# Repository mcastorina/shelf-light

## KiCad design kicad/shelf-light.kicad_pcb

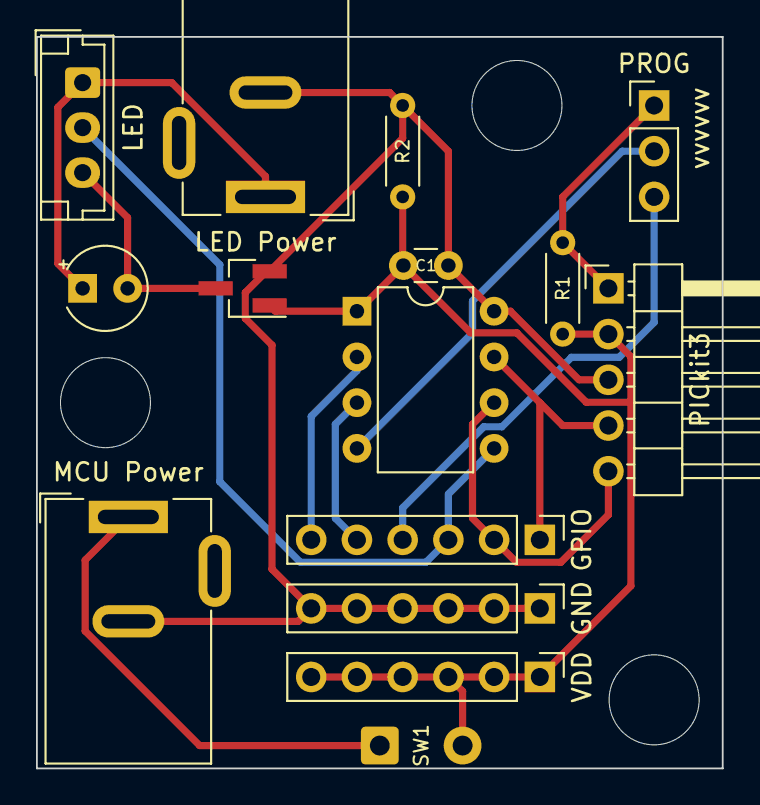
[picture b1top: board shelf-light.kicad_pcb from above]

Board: 2 copper layers, 38.1 x 40.6 mm, 18 parts (0 on the bottom side), 13 nets.

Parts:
C1: 100nF; C_Disc_D3.0mm_W1.6mm_P2.50mm
C2: 100mF; CP_Radial_Tantal_D4.5mm_P2.50mm
GND: GND; PinHeader_1x06_P2.54mm_Vertical
GPIO: GPIO; PinHeader_1x06_P2.54mm_Vertical
H1, H2, H3: MountingHole; MountingHole_5mm
LED: LED; JST_EH_B3B-EH-A_1x03_P2.50mm_Vertical
LED Power: LED Power; BarrelJack_Wuerth_6941xx301002
MCU Power: MCU Power; BarrelJack_Wuerth_6941xx301002
PICkit3: PICkit3; PinHeader_1x05_P2.54mm_Horizontal
PROG: vvvvvv; PinHeader_1x03_P2.54mm_Vertical
Q1: NDS355AN; SOT-23_Handsoldering
R1, R2: 10k; R_Axial_DIN0204_L3.6mm_D1.6mm_P5.08mm_Horizontal
SW1: Switch; SolderWire-0.5sqmm_1x02_P4.6mm_D0.9mm_OD2.1mm
U1: PIC16F15313; DIP-8_W7.62mm
VDD: VDD; PinHeader_1x06_P2.54mm_Vertical

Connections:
GND: C1.1, GND.1, GND.2, GND.3, GND.4, GND.5, GND.6, LED Power.2, MCU Power.2, PICkit3.3, Q1.2, R2.2, U1.8
unnamed: C2.1, LED.1, LED Power.1
unnamed: C2.2, LED.3, Q1.3
unnamed: PICkit3.1, PROG.1, R1.2
unnamed: GPIO.1, PICkit3.4, U1.7
unnamed: GPIO.2, PICkit3.5, U1.6
unnamed: MCU Power.1, SW1.1
unnamed: GPIO.3, LED.2, U1.5
unnamed: GPIO.4, PROG.3
unnamed: GPIO.5, U1.3
unnamed: GPIO.6, U1.2
unnamed: PROG.2, U1.4
VDD: C1.2, PICkit3.2, Q1.1, R1.1, R2.1, SW1.2, U1.1, VDD.1, VDD.2, VDD.3, VDD.4, VDD.5, VDD.6

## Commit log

2020-09-07 Arduino POC
    This sketch uses a potentiometer to calculate the warmth value as a
    function of hue. Hue is then converted to RGB, and a library writes the
    data to the LED strip.
2020-09-09 Implement stable analog read
    To get a stable reading, we take the average of 10 successive reads.
2020-09-09 Update the LED strip only if the color has changed
2020-09-09 Use low power sleep instead of delay
2020-09-10 Add current measurements
2020-10-10 Add MPLabX project for programming the PIC
    The main.c file successfully writes to the LED strip, but needs to be
    expanded to include reading the potentiometer and dynamically updating
    the color.
2020-10-10 Add gitignore for arduino-uno
2020-10-12 Implement analog read and color changing logic
    The ADC is configured to read an analog value from RA4 using Vdd as a
    voltage reference. That value is then converted to a number between 120
    and 360 to be used as the hue value in HSV to RGB conversion.
    Converting from HSV normally uses floating points, but to save
    programming memory it is implemented as fixed point with two decimal
    places.
2020-10-15 Add second potentiometer to control color value (brightness)
2023-04-06 Add kicad files
2023-04-06 Rename kicad project
    If the project fails to load because of the rename, the previous commit
    should work (with the project name of test).
